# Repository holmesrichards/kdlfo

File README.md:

# Shape variable dual LFO

This is a dual LFO synth module in Kosmo format, based on a [Kassutronics design](https://kassu2000.blogspot.com/2015/10/variable-waveshape-lfo.html). There are three outputs for each LFO. Depending on the shape pot setting these provide ramp, asymmetric triangle, symmetric triangle, or sawtooth waveforms; sine or skewed "sine" waveforms; and narrow, square, or wide pulse waveforms respectively.

Version 1.0 corrects some first run problems. Version 1.0 PCB has not been tested.

## Current draw
32 mA +12 V, 32 mA -12 V

## Photos

## Documentation

* [Schematic](Docs/kdlfo.pdf)
* PCB layout: [front](Docs/kdlfo_layout_front.pdf), [back](Docs/kdlfo_layout_back.pdf)
* [BOM](Docs/kdlfo_bom.md)
* [Build notes](Docs/build.md)
* [Blog post](https://analogoutputblog.wordpress.com/2022/05/11/kassutronics-dual-lfo/)

## GitHub repository

* [https://github.com/holmesrichards/duallfo](https://github.com/holmesrichards/kdlfo)

## Submodules

This repo uses submodules aoKicad and Kosmo_panel, which provide needed libaries for KiCad. To clone:

```
git clone git@github.com:holmesrichards/kdlfo.git
git submodule init
git submodule update
```

Alternatively do

```
git clone --recurse-submodules git@github.com:holmesrichards/kdlfo.git
```

Or if you download the repository as a zip file, you must also click on the "aoKicad" and "Kosmo\_panel" links on the GitHub page (they'll have "@ something" after them) and download them as separate zip files which you can unzip into this repo's aoKicad and Kosmo\_panel directories.

If desired, copy the files from aoKicad and Kosmo\_panel to wherever you prefer (your KiCad user library directory, for instance, if you have one). Then in KiCad, go into Edit Symbols and add symbol libraries 

```
aoKicad/ao_symbols
Kosmo_panel/Kosmo
```
and go into Edit Footprints and add footprint libraries 
```
aoKicad/ao_tht
Kosmo_panel/Kosmo_panel.
```

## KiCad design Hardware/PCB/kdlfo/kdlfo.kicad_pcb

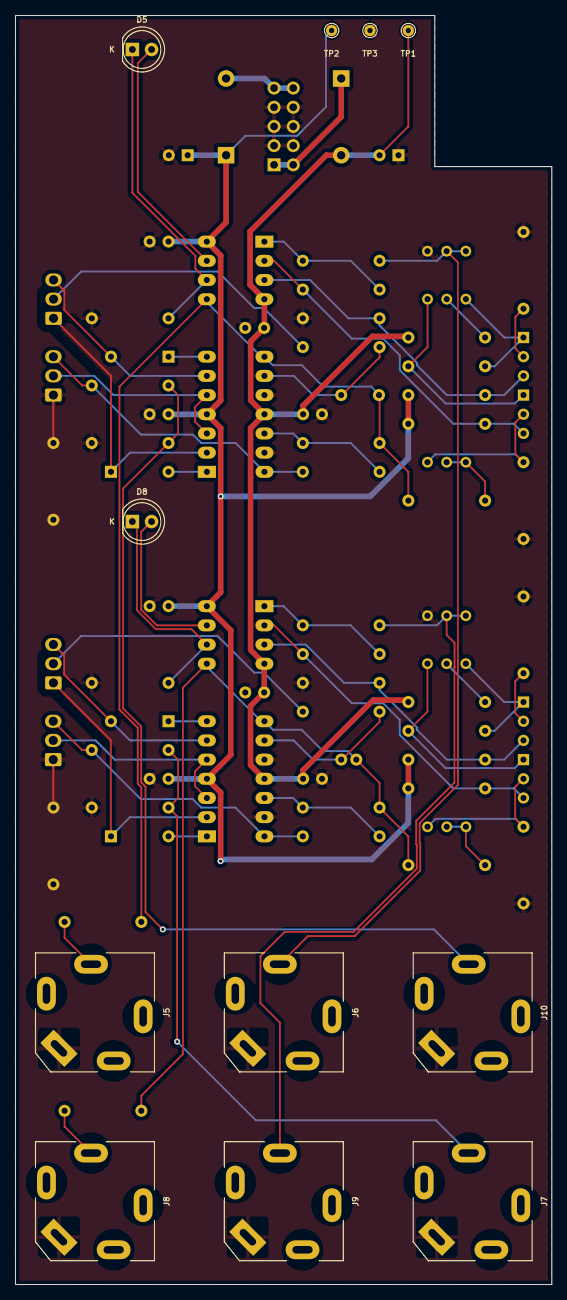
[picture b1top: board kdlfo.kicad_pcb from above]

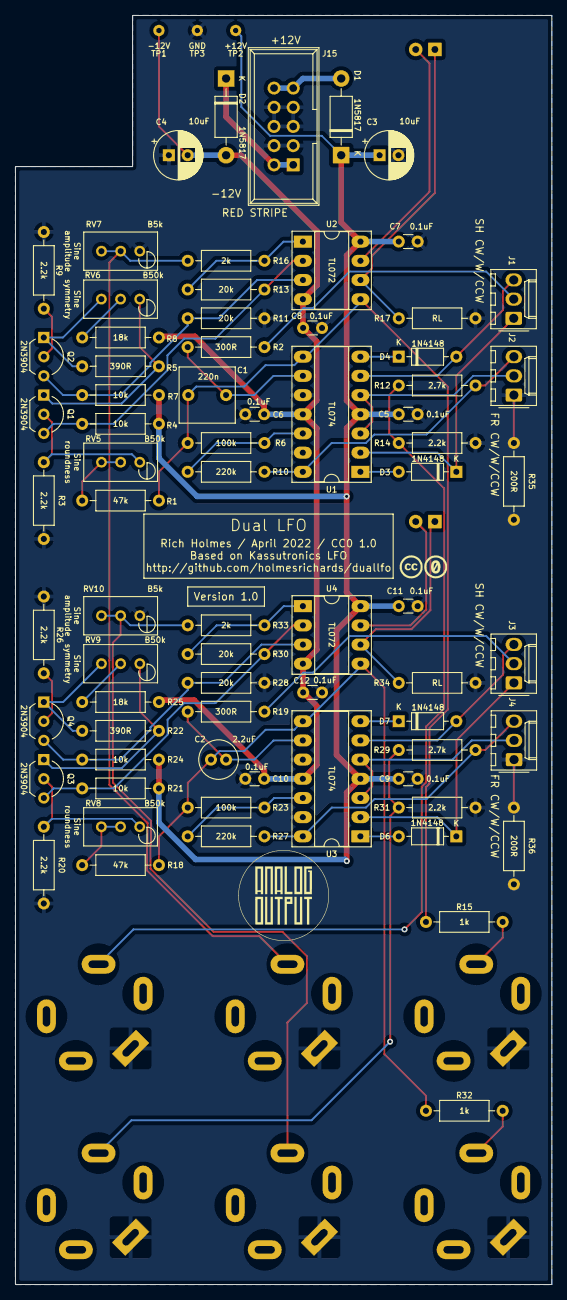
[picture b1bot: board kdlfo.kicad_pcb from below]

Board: 2 copper layers, 71.0 x 168.0 mm, 87 parts (75 on the bottom side), 55 nets.

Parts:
C1: 220n; C_Rect_L7.2mm_W7.2mm_P5.00mm_FKS2_FKP2_MKS2_MKP2
C2: 2.2uF; C_Radial_D5.0mm_H11.0mm_P2.00mm
C3, C4: 10uF; CP_Radial_D6.3mm_P2.50mm
C5, C6, C7, C8, C9, C10, C11, C12: 0.1uF; C_Disc_D3.0mm_W1.6mm_P2.50mm
D1, D2: 1N5817; D_DO-41_SOD81_P10.16mm_Horizontal
D3, D4, D6, D7: 1N4148; D_DO-35_SOD27_P7.62mm_Horizontal
D5, D8: LED_Dual_2pin; LED_D5.0mm
GRAF1: Holes; kdlfo_panel_holes
GRAF2: CC0 logo; CC0_logo
GRAF3: AO logo; analogoutput_12mm
J1, J2, J3, J4: 3_pin_Molex_header; Molex_KK-254_AE-6410-03A_1x03_P2.54mm_Vertical
J5, J6, J7, J8, J9, J10: AudioJack2; Jack_6.35mm_PJ_629HAN_slots
J15: Synth_power_2x5; Power_Header
Q1, Q2, Q3, Q4: 2N3904; TO-92_Inline_Wide
R1, R18: 47k; R_Axial_DIN0207_L6.3mm_D2.5mm_P10.16mm_Horizontal
R2, R19: 300R; R_Axial_DIN0207_L6.3mm_D2.5mm_P10.16mm_Horizontal
R3, R9, R14, R20, R26, R31: 2.2k; R_Axial_DIN0207_L6.3mm_D2.5mm_P10.16mm_Horizontal
R4, R7, R21, R24: 10k; R_Axial_DIN0207_L6.3mm_D2.5mm_P10.16mm_Horizontal
R5, R22: 390R; R_Axial_DIN0207_L6.3mm_D2.5mm_P10.16mm_Horizontal
R6, R23: 100k; R_Axial_DIN0207_L6.3mm_D2.5mm_P10.16mm_Horizontal
R8, R25: 18k; R_Axial_DIN0207_L6.3mm_D2.5mm_P10.16mm_Horizontal
R10, R27: 220k; R_Axial_DIN0207_L6.3mm_D2.5mm_P10.16mm_Horizontal
R11, R13, R28, R30: 20k; R_Axial_DIN0207_L6.3mm_D2.5mm_P10.16mm_Horizontal
R12, R29: 2.7k; R_Axial_DIN0207_L6.3mm_D2.5mm_P10.16mm_Horizontal
R15, R32: 1k; R_Axial_DIN0207_L6.3mm_D2.5mm_P10.16mm_Horizontal
R16, R33: 2k; R_Axial_DIN0207_L6.3mm_D2.5mm_P10.16mm_Horizontal
R17, R34: RL; R_Axial_DIN0207_L6.3mm_D2.5mm_P10.16mm_Horizontal
R35, R36: 200R; R_Axial_DIN0207_L6.3mm_D2.5mm_P10.16mm_Horizontal
RV5, RV6, RV8, RV9: B50k; Potentiometer_Bourns_3296W_Vertical_standard
RV7, RV10: B5k; Potentiometer_Bourns_3296W_Vertical_standard
TP1: -12V; TestPoint_THTPad_D1.5mm_Drill0.7mm
TP2: +12V; TestPoint_THTPad_D1.5mm_Drill0.7mm
TP3: GND; TestPoint_THTPad_D1.5mm_Drill0.7mm
U1, U3: TL074; DIP-14_W7.62mm_Socket_LongPads
U2, U4: TL072; DIP-8_W7.62mm_Socket_LongPads

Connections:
+12V: C3.1, C5.1, C7.1, C9.1, C11.1, D1.1 (K), R4.1, R7.1, R21.1, R24.1, TP2.1, U1.4 (V+), U2.8 (V+), U3.4 (V+), U4.8 (V+)
-12V: C4.2, C6.2, C8.2, C10.2, C12.2, D2.2 (A), R8.1, R25.1, TP1.1, U1.11 (V-), U2.4 (V-), U3.11 (V-), U4.4 (V-)
/+12_IN: D1.2 (A), J15.9 (+12V), J15.10 (+12V)
/-12_IN: D2.1 (K), J15.1 (-12V), J15.2 (-12V)
/LFO A/CAP1: C1.1, R2.2, U1.9 (-)
/LFO A/CAP2: C1.2, R1.2, R6.2, R15.2, U1.8, U2.5 (+)
/LFO A/FRPOTCCW: J2.1, R35.1
/LFO A/FRPOTCW: J2.3, R10.1, R12.2, U1.14
/LFO A/FRPOTW: J2.2, U1.3 (+), U1.5 (+)
/LFO A/SHPOTCCW: D3.1 (K), J1.1, U1.2 (-)
/LFO A/SHPOTCW: D4.2 (A), J1.3, U1.6 (-)
/LFO A/SHPOTW: J1.2, R2.1
/LFO A/SINE_ROUND: R1.1, RV5.2, RV5.3
/LFO A/SINE_SYM: R8.2, RV6.2
/LFO B/CAP1: C2.1, R19.2, U3.9 (-)
/LFO B/CAP2: C2.2, R18.2, R23.2, R32.2, U3.8, U4.5 (+)
/LFO B/FRPOTCCW: J4.1, R36.1
/LFO B/FRPOTCW: J4.3, R27.1, R29.2, U3.14
/LFO B/FRPOTW: J4.2, U3.3 (+), U3.5 (+)
/LFO B/SHPOTCCW: D6.1 (K), J3.1, U3.2 (-)
/LFO B/SHPOTCW: D7.2 (A), J3.3, U3.6 (-)
/LFO B/SHPOTW: J3.2, R19.1
/LFO B/SINE_ROUND: R18.1, RV8.2, RV8.3
/LFO B/SINE_SYM: R25.2, RV9.2
/SINE_A: J6.T, R16.1, RV7.2, RV7.3
/SINE_B: J9.T, R33.1, RV10.2, RV10.3
/SQPULSE_A: J10.T, R12.1, R14.1
/SQPULSE_B: J7.T, R29.1, R31.1
/TRIRAMP_A: J5.T, R15.1
/TRIRAMP_B: J8.T, R32.1
GND: C3.2, C4.1, C5.2, C6.1, C7.2, C8.1, C9.2, C10.1, C11.2, C12.1, J5.S, J6.S, J7.S, J8.S, J9.S, J10.S, J15.3 (GND), J15.4 (GND), J15.5 (GND), J15.6 (GND), J15.7 (GND), J15.8 (GND), R3.2, R9.2, R11.2, R14.2, R17.2, R20.2, R26.2, R28.2, R31.2, R34.2, R35.2, R36.2, RV7.1, RV10.1, TP3.1, U1.10 (+), U1.13 (-), U3.10 (+), U3.13 (-)
unnamed: D3.2 (A), U1.1
unnamed: D4.1 (K), U1.7
unnamed: D5.1 (KA), R17.1, U2.6 (-)
unnamed: D5.2 (AK), U2.7
unnamed: D6.2 (A), U3.1
unnamed: D7.1 (K), U3.7
unnamed: D8.1 (KA), R34.1, U4.6 (-)
unnamed: D8.2 (AK), U4.7
unnamed: Q1.1 (E), R5.2, RV6.1
unnamed: Q1.2 (B), R3.1, RV5.1
unnamed: Q1.3 (C), R4.2, R13.2, U2.2 (-)
unnamed: Q2.1 (E), R5.1, RV6.3
unnamed: Q2.2 (B), R9.1
unnamed: Q2.3 (C), R7.2, R11.1, U2.3 (+)
unnamed: Q3.1 (E), R22.2, RV9.1
unnamed: Q3.2 (B), R20.1, RV8.1
unnamed: Q3.3 (C), R21.2, R30.2, U4.2 (-)
unnamed: Q4.1 (E), R22.1, RV9.3
unnamed: Q4.2 (B), R26.1
unnamed: Q4.3 (C), R24.2, R28.1, U4.3 (+)
unnamed: R6.1, R10.2, U1.12 (+)
unnamed: R13.1, R16.2, U2.1
unnamed: R23.1, R27.2, U3.12 (+)
unnamed: R30.1, R33.2, U4.1

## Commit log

2021-11-25 Initial version
2021-11-25 Replace sine shaper, add divider on pulse output
2021-11-25 Panel svg
2021-12-02 Panel art
2021-12-05 README edit
2021-12-22 revise panel
2021-12-25 README
2022-02-01 Better .gitignore; rm extraneous footprint library; misc revisions
2022-03-28 Reorg schematic, redo layout
2022-03-28 Reorg schematic, redo layout some more
2022-04-03 Fix LED
2022-04-03 panel
2022-04-06 Colorize net classes
2022-05-02 Final pre fab tweaks, Gerbers
2022-05-02 Slotted jack footprints you idiot
2022-05-02 Front panel label -> Kassutronics
2022-05-11 Post fab updates
2022-05-11 LICENSE
2022-05-11 Blog post
2022-05-11 Fix silkscreen errors and omissions, change integ resistor, add shape resistor
2022-05-11 V1.0 untested PCB note
2022-05-15 Schematic annotations
2022-05-23 Current draw

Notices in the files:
Hardware/PCB/kdlfo/kdlfo.kicad_pcb:
Rich Holmes / April 2022 / CC0 1.0
